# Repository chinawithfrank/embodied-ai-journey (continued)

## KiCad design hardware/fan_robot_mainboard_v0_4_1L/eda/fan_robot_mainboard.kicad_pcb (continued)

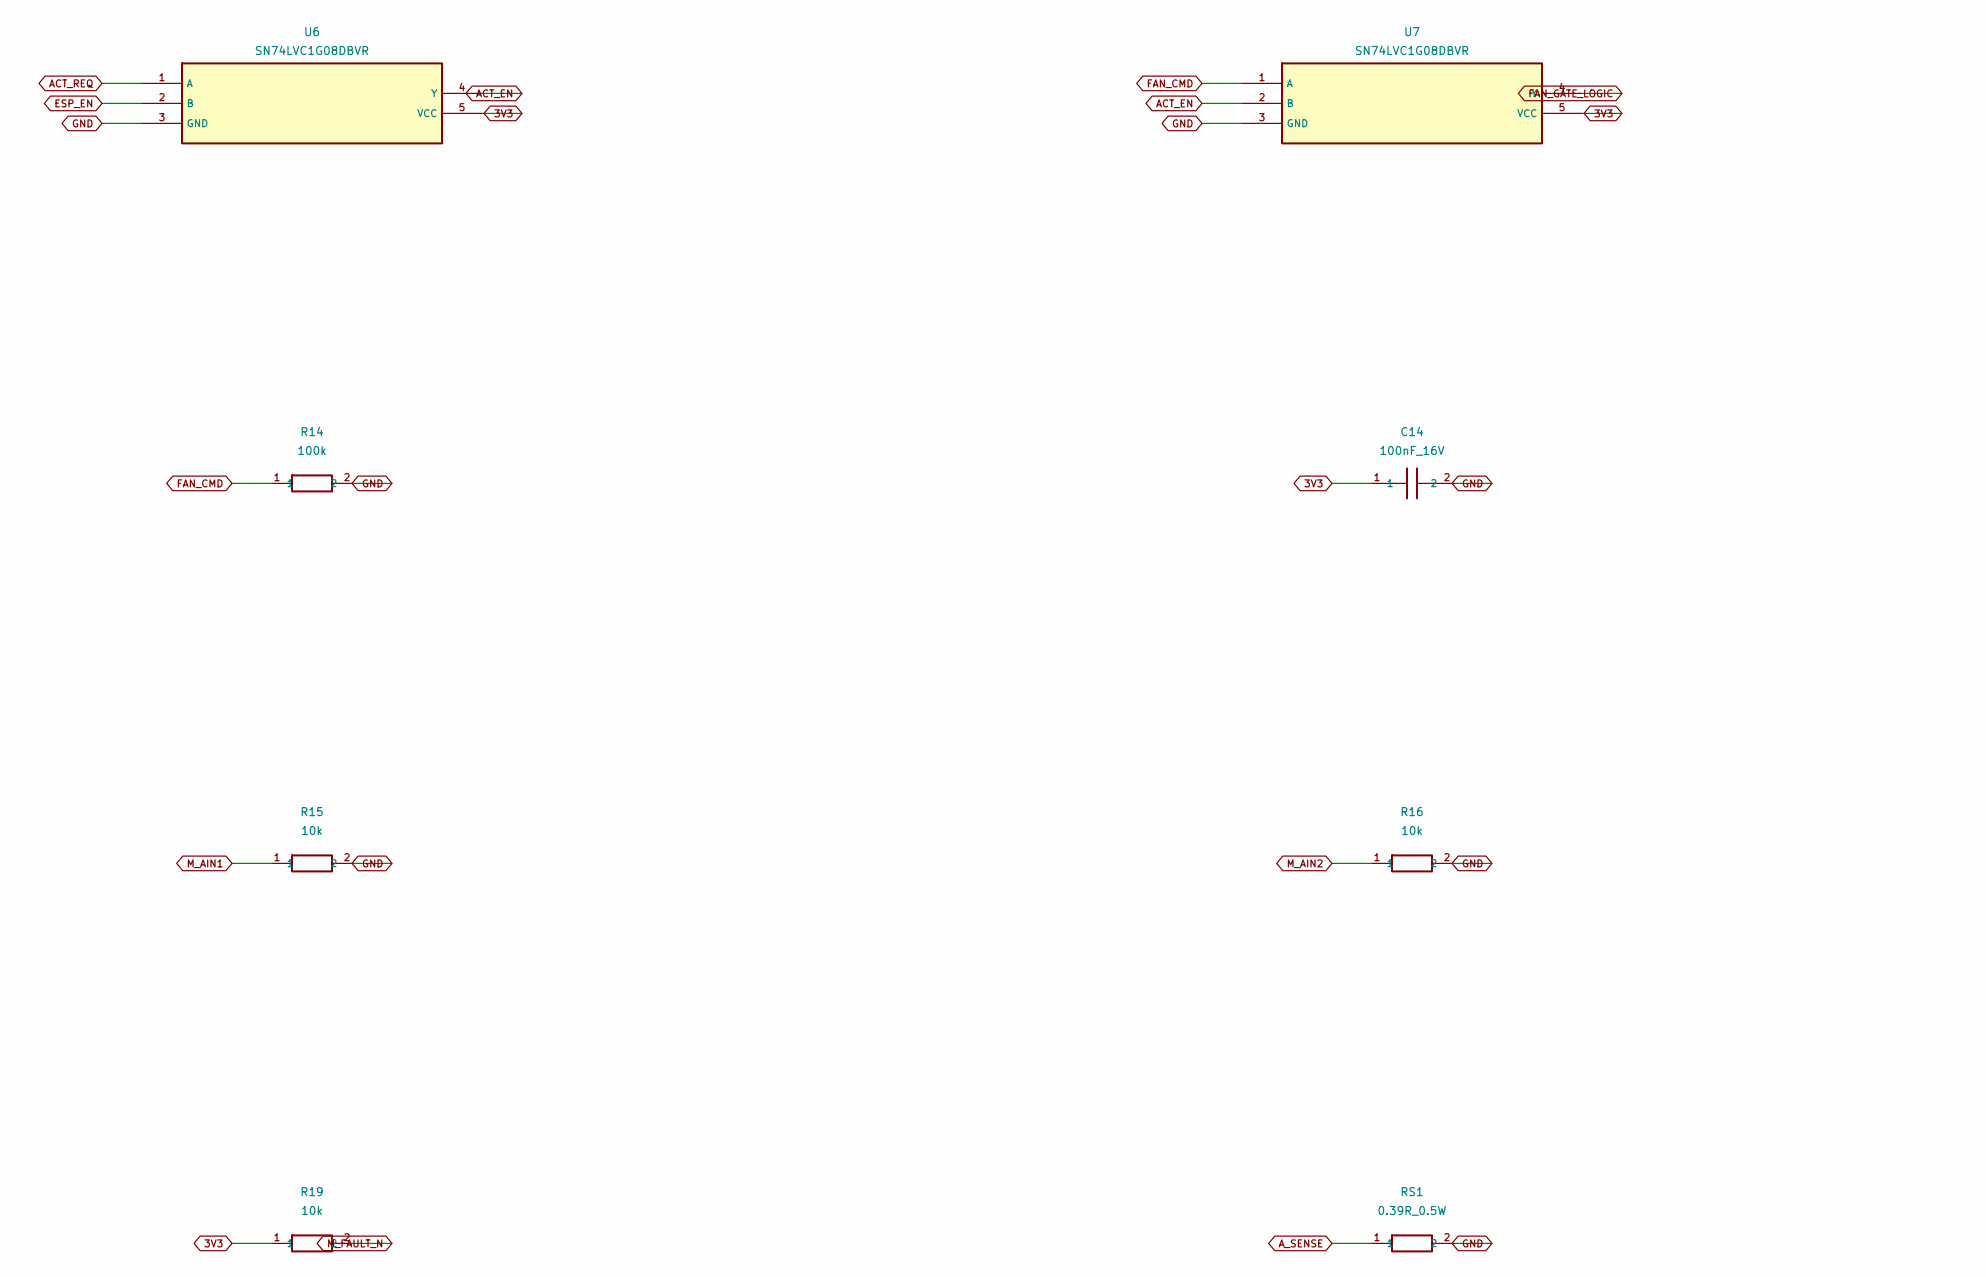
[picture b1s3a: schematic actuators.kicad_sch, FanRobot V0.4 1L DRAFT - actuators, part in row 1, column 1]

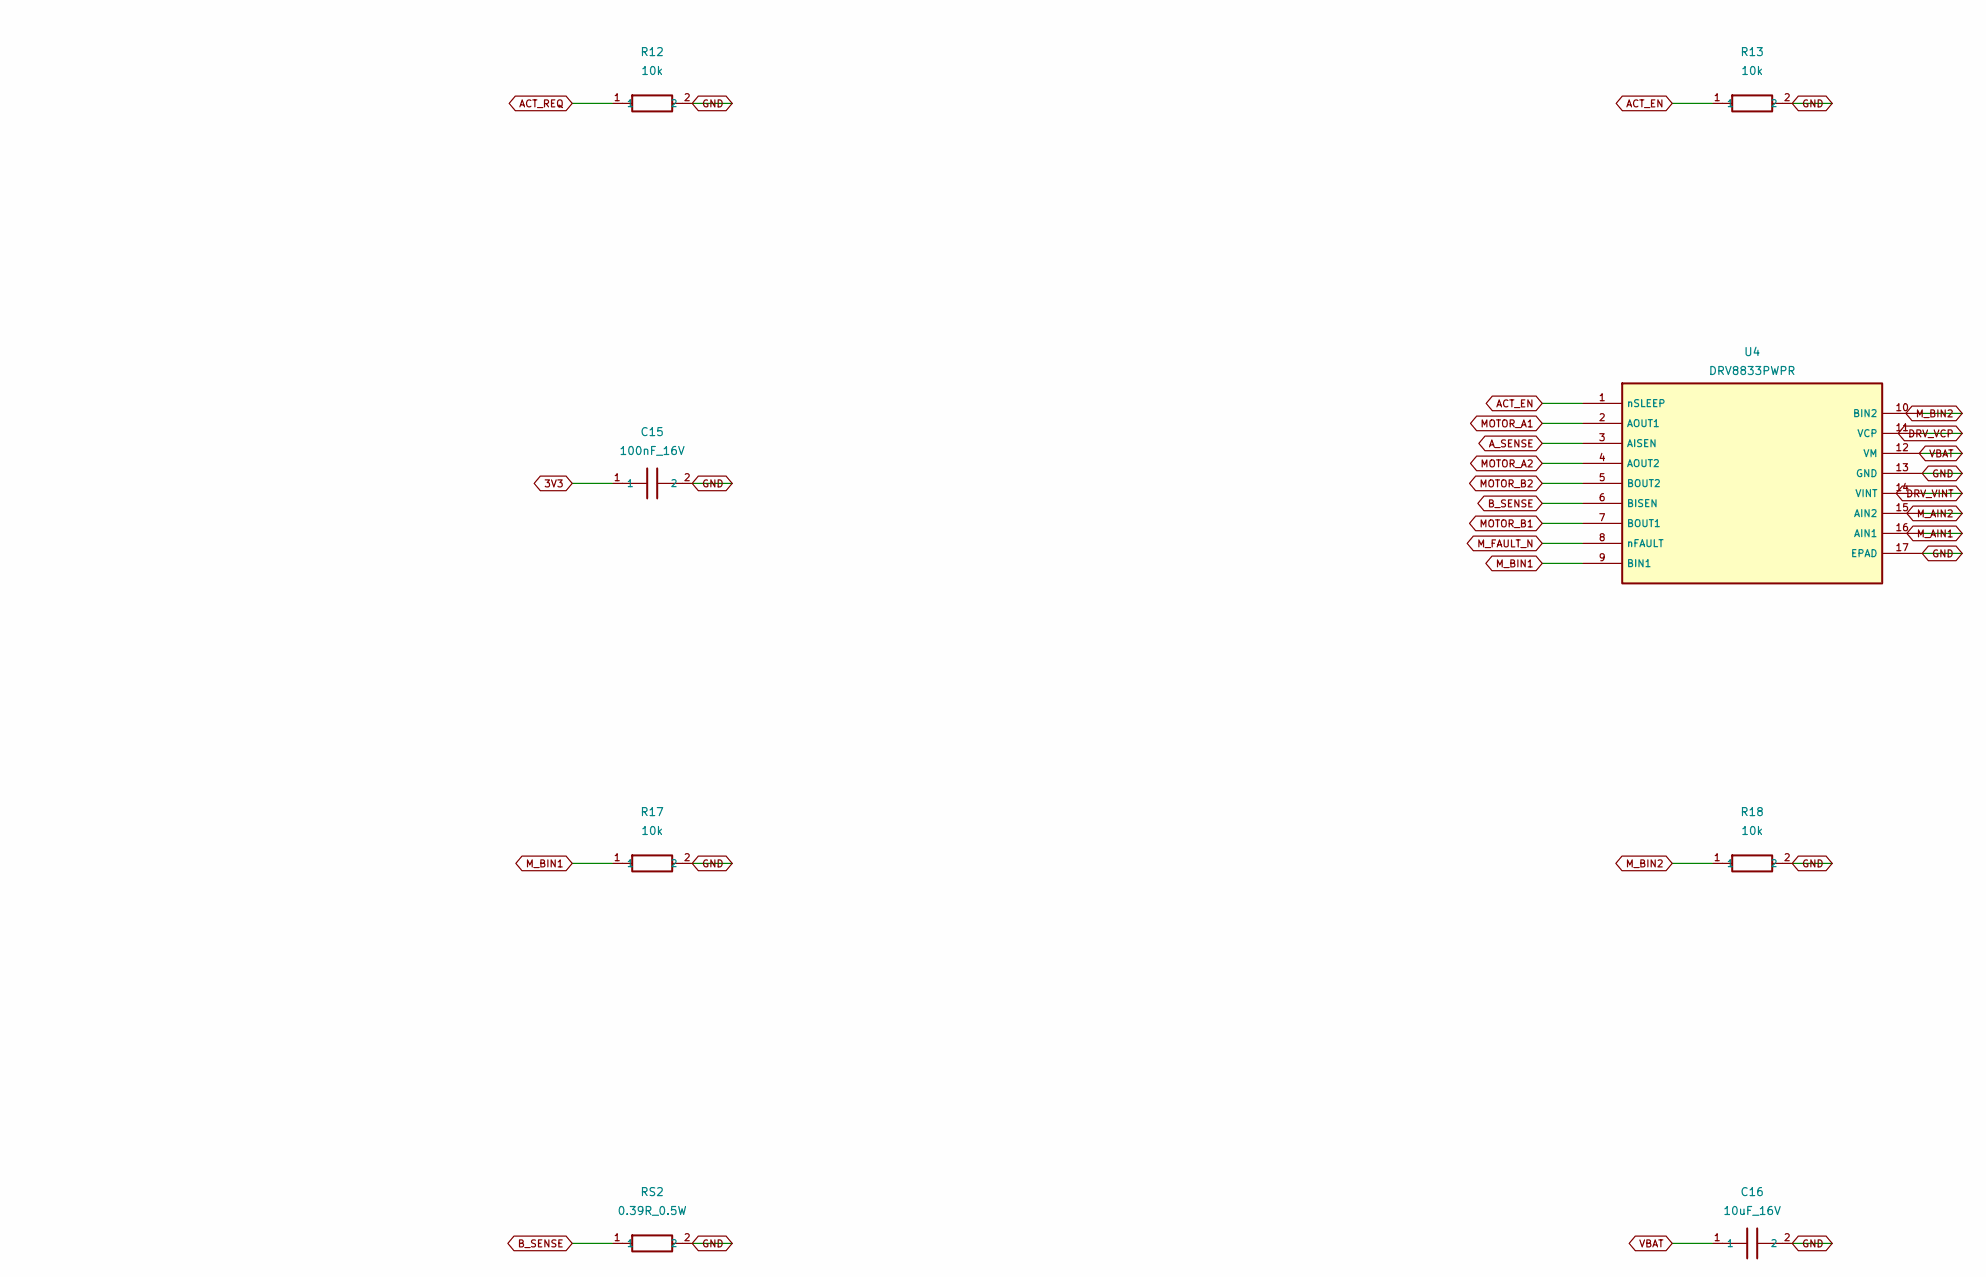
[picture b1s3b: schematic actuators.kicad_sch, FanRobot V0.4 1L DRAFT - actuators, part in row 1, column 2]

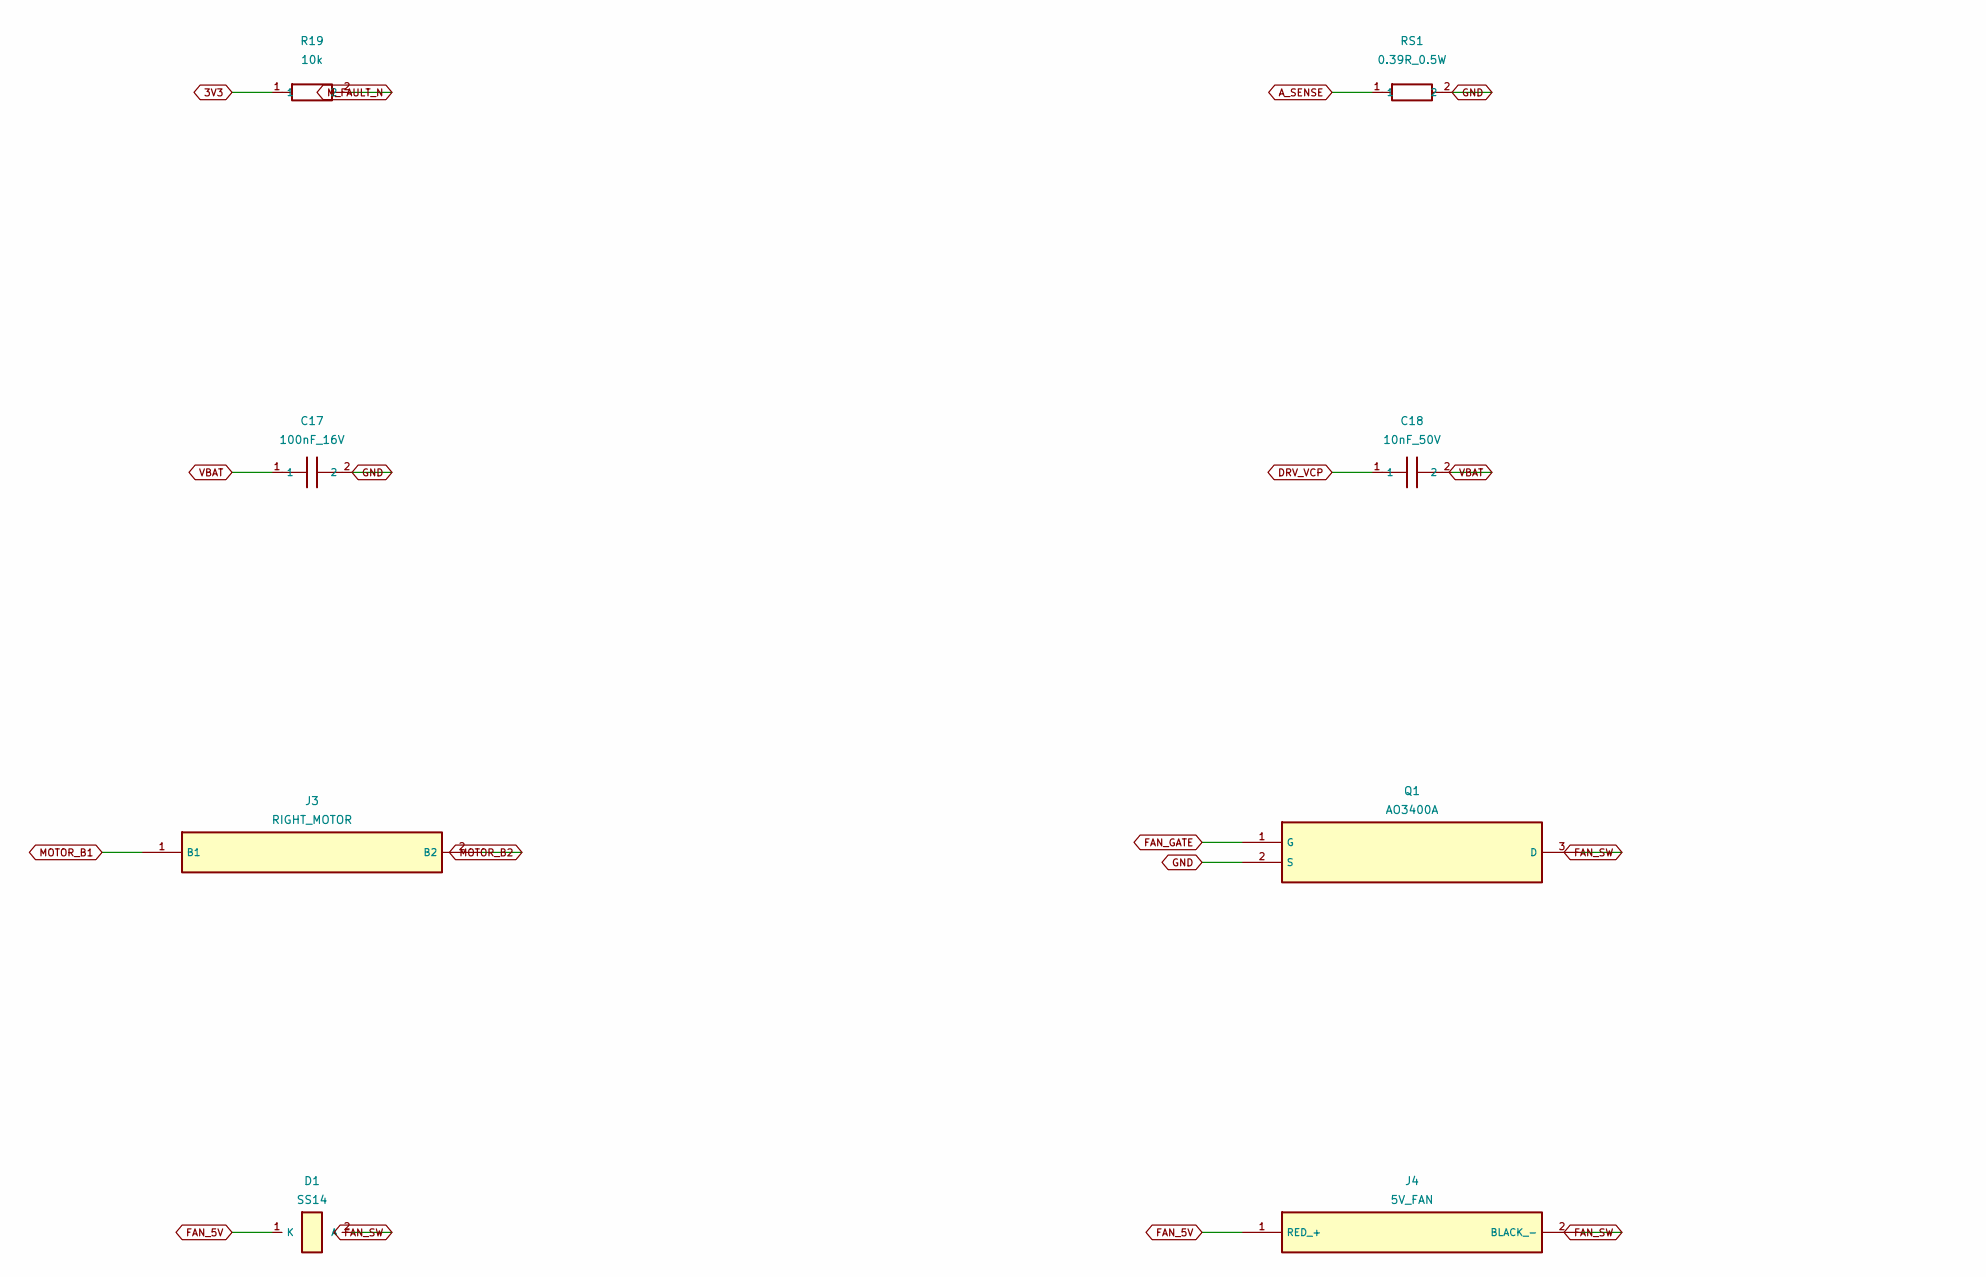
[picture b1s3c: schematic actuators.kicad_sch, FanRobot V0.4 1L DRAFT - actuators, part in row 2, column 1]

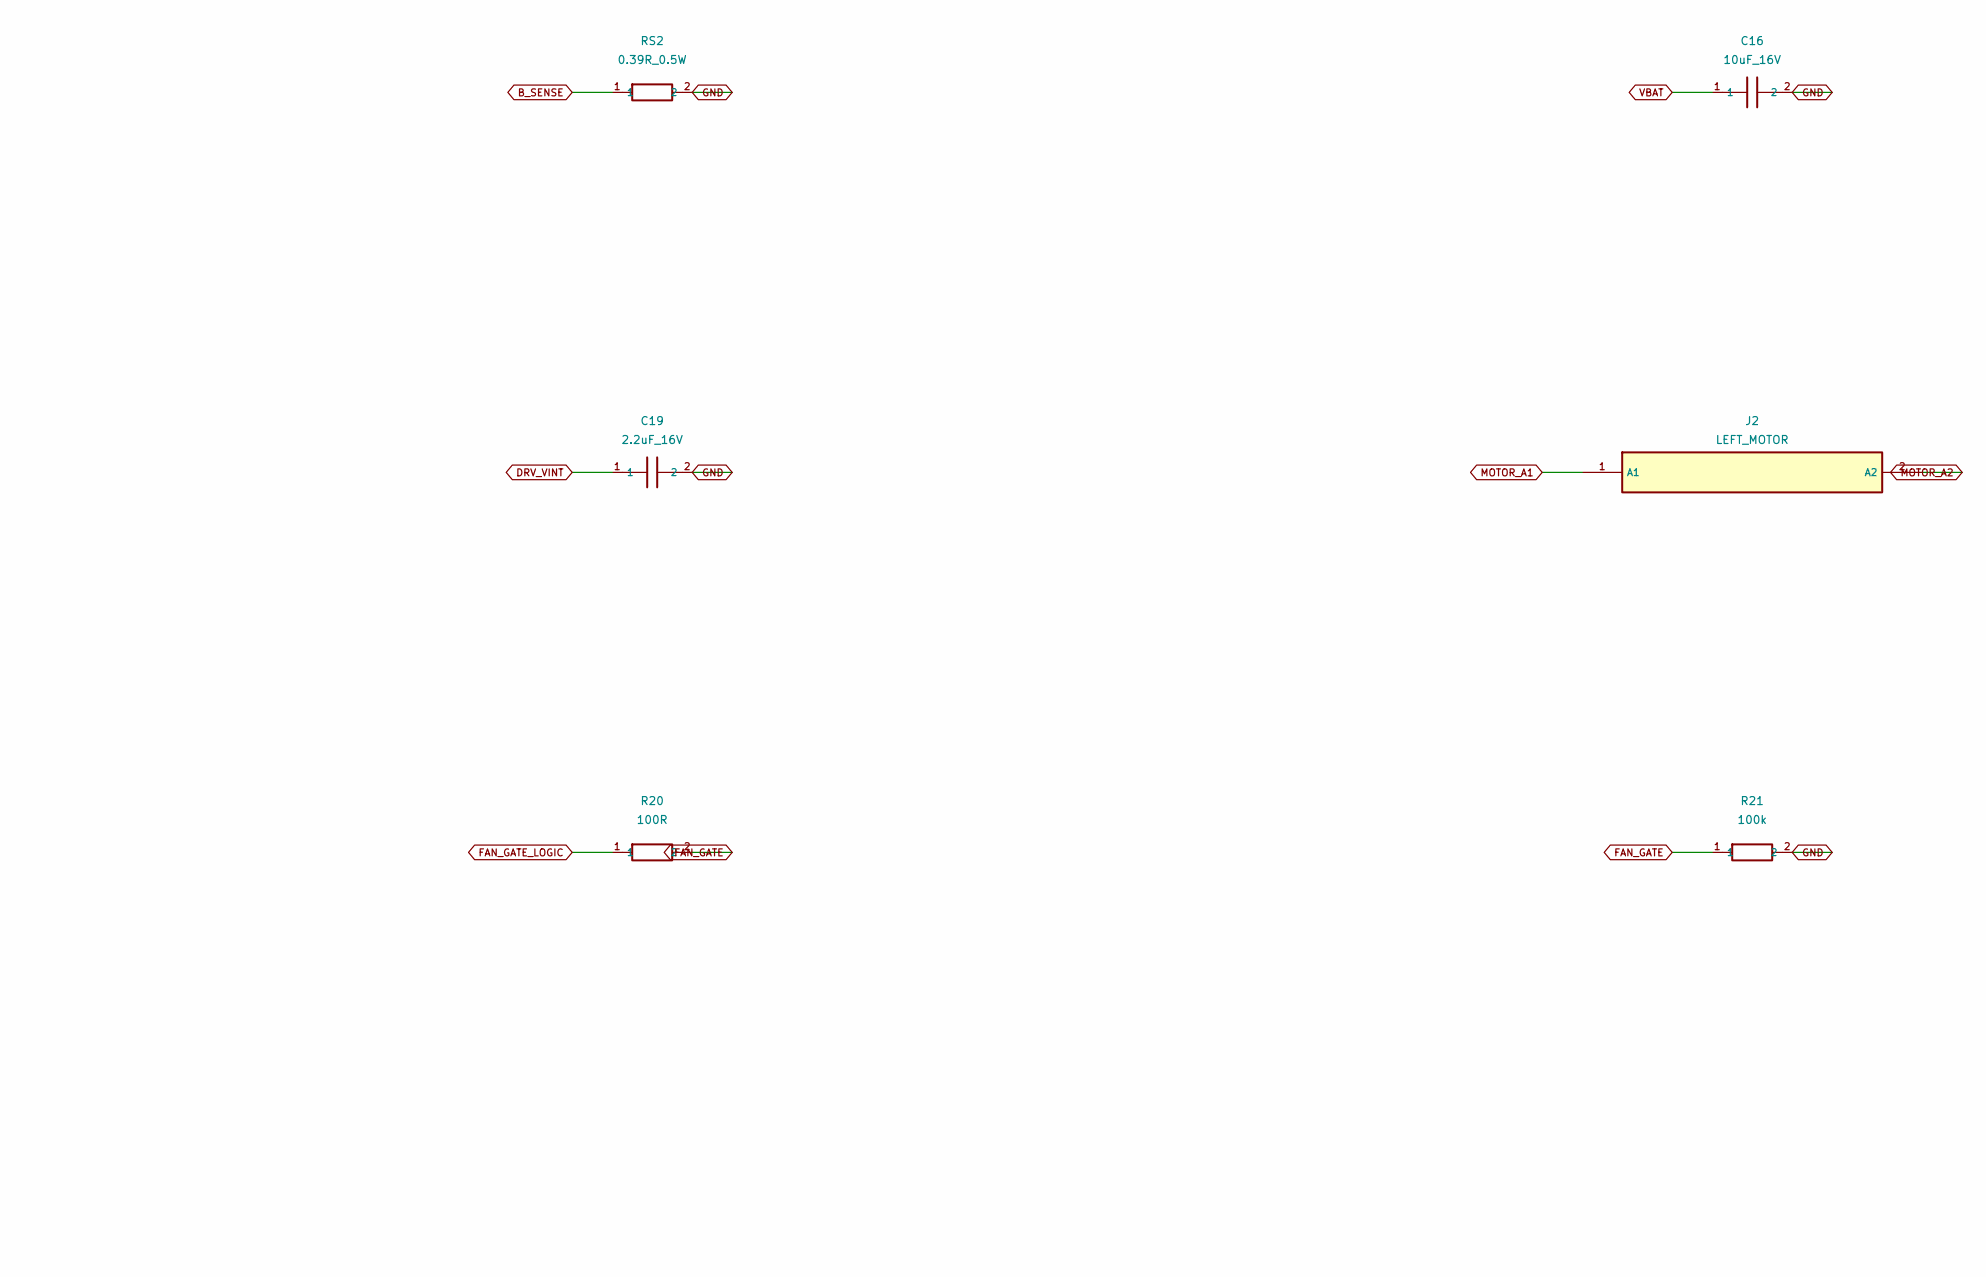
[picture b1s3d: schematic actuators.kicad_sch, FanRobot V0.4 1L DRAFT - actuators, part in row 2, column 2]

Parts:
C14, C15, C17: 100nF_16V; C_0603_1608Metric; MPN GRM188R71C104KA01D; LCSC C45000
C16: 10uF_16V; C_0805_2012Metric; MPN GRM21BR61C106KE15L; LCSC C77075
C18: 10nF_50V; C_0603_1608Metric; MPN CL10B103KB8NNNC; LCSC C1589
C19: 2.2uF_16V; C_0805_2012Metric; MPN GRM21BR71C225KA12L; LCSC C108378
D1: SS14; D_SMA; MPN SS14; LCSC C2480
J2: LEFT_MOTOR; JST_PH_B2B-PH-K_1x02_P2.00mm_Vertical; MPN B2B-PH-K-S(LF)(SN); LCSC C131337
J3: RIGHT_MOTOR; JST_PH_B2B-PH-K_1x02_P2.00mm_Vertical; MPN B2B-PH-K-S(LF)(SN); LCSC C131337
J4: 5V_FAN; JST_PH_B2B-PH-K_1x02_P2.00mm_Vertical; MPN B2B-PH-K-S(LF)(SN); LCSC C131337
Q1: AO3400A; SOT-23; MPN AO3400A; LCSC C20917
R12, R13, R15, R16, R17, R18, R19: 10k; R_0603_1608Metric; MPN 0603WAF1002T5E; LCSC C25804
R14, R21: 100k; R_0603_1608Metric; MPN 0603WAF1003T5E; LCSC C25803
R20: 100R; R_0603_1608Metric; MPN 0603WAF1000T5E; LCSC C22775
RS1, RS2: 0.39R_0.5W; R_1206_3216Metric; MPN RL12FTNR390; LCSC C188072
U4: DRV8833PWPR; HTSSOP-16-1EP_4.4x5mm_P0.65mm_EP3.4x5mm_Mask2.46x2.31mm; MPN DRV8833PWPR; LCSC C50506
U6, U7: SN74LVC1G08DBVR; SOT-23-5; MPN SN74LVC1G08DBVR; LCSC C7666

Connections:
3V3: C14.1, C15.1, R19.1, U6.5 (VCC), U7.5 (VCC); also elsewhere on the board
ACT_EN: R13.1, U4.1 (nSLEEP), U6.4 (Y), U7.2 (B); also elsewhere on the board
ACT_REQ: R12.1, U6.1 (A); also elsewhere on the board
A_SENSE: RS1.1, U4.3 (AISEN)
B_SENSE: RS2.1, U4.6 (BISEN)
DRV_VCP: C18.1, U4.11 (VCP)
DRV_VINT: C19.1, U4.14 (VINT)
ESP_EN: U6.2 (B); also elsewhere on the board
FAN_5V: D1.1 (K), J4.1 (RED_+); also elsewhere on the board
FAN_CMD: R14.1, U7.1 (A); also elsewhere on the board
FAN_GATE: Q1.1 (G), R20.2, R21.1
FAN_GATE_LOGIC: R20.1, U7.4 (Y)
FAN_SW: D1.2 (A), J4.2 (BLACK_-), Q1.3 (D)
GND: C14.2, C15.2, C16.2, C17.2, C19.2, Q1.2 (S), R12.2, R13.2, R14.2, R15.2, R16.2, R17.2, R18.2, R21.2, RS1.2, RS2.2, U4.13 (GND), U4.17 (EPAD), U6.3 (GND), U7.3 (GND); also elsewhere on the board
MOTOR_A1: J2.1 (A1), U4.2 (AOUT1)
MOTOR_A2: J2.2 (A2), U4.4 (AOUT2)
MOTOR_B1: J3.1 (B1), U4.7 (BOUT1)
MOTOR_B2: J3.2 (B2), U4.5 (BOUT2)
M_AIN1: R15.1, U4.16 (AIN1); also elsewhere on the board
M_AIN2: R16.1, U4.15 (AIN2); also elsewhere on the board
M_BIN1: R17.1, U4.9 (BIN1); also elsewhere on the board
M_BIN2: R18.1, U4.10 (BIN2); also elsewhere on the board
M_FAULT_N: R19.2, U4.8 (nFAULT); also elsewhere on the board
VBAT: C16.1, C17.1, C18.2, U4.12 (VM); also elsewhere on the board
